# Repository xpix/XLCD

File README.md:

XStepperLCD
===========

LCD Module for XStepper

Some time ago, we designed and built version 1.0 of Xstepper.  Unlike other existing GRBL-based CNC solutions, Xstepper is an all-in-one device.  The possibility of controlling the machine in a headless state may be possible, and the first step toward doing so is some sort of visual display.  This module aims at solving part of the problem!

But how?  The good people coding GRBL dont have the on-chip memory to code in an LCD interface for GRBL.  Add to that the severe lack of available IO and this seems to rule out this type of expansion.  However, there is always a workaround.

This module spies on the serial communication between the arduino and PC using an ATtiny85.  Simultaneously the ATtimy polls the position of the spindle from the XStepper.  The returned data is then parsed and displayed on a local LCD.  You can choose to display the debug screen, work position or machine position using the on-board button.

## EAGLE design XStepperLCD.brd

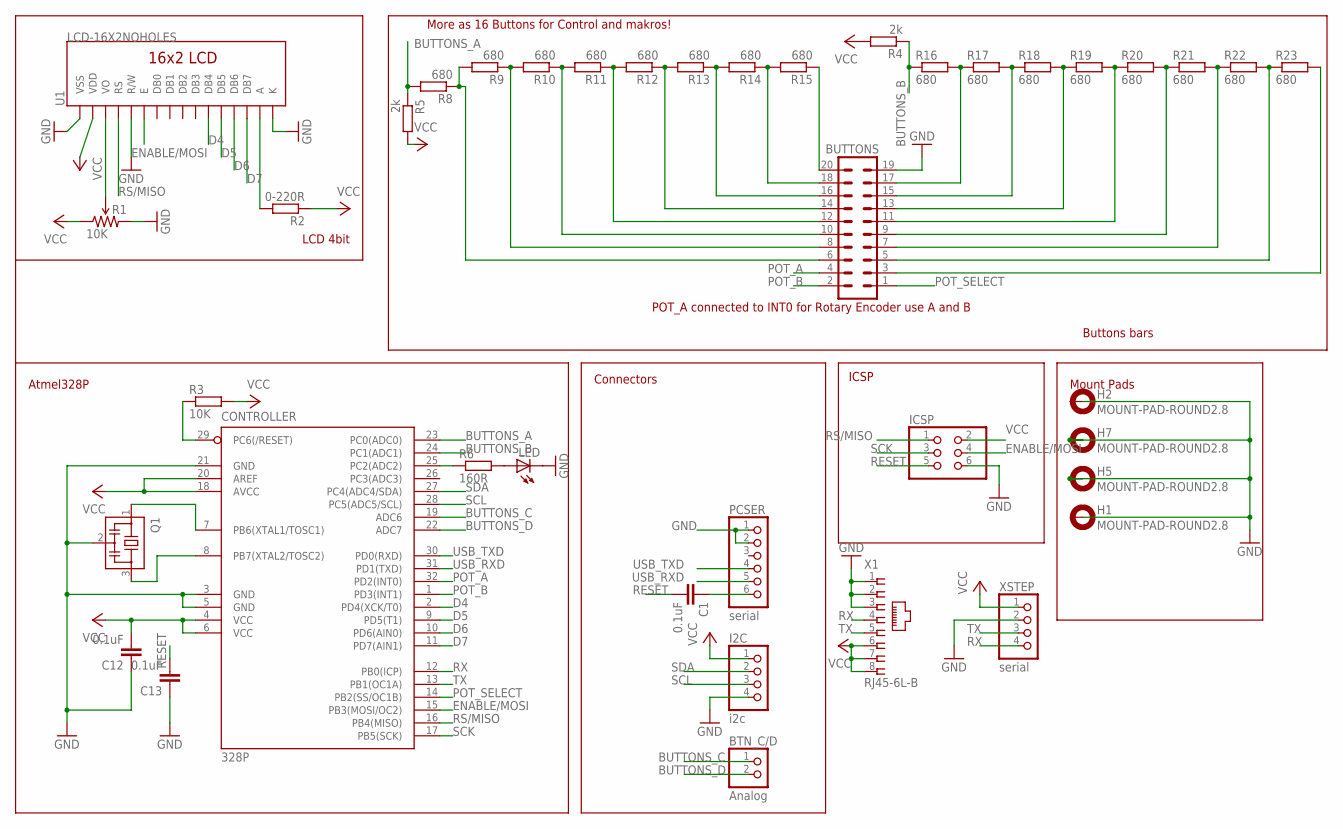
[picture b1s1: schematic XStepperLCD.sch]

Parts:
328P: CONTROLLER; TQFP32-08
BTN_C/D: Analog; 1X02
BUTTONS: ML20
C1, C12, C13: 0.1uF; C1206
H1, H2, H5, H7: MOUNT-PAD-ROUND2.8; 2,8-PAD
I2C: i2c; 1X04/90
ICSP: PINHD-2X3; 2X03
LED: LEDSMT1206; 1206
PCSER: serial; 1X06/90
Q1: CSTCR6M00G53Z; CSTCR6M
R1: 10K; 3362U-2
R2: 0-220R; R1206
R3: 10K; R1206
R4, R5: 2k; R1206
R6: 160R; R1206
R8, R9, R10, R11, R12, R13, R14, R15, R16, R17, R18, R19, R20, R21, R22, R23: 680; R1206
U1: LCD-16X2NOHOLES; LCD-16X2_NOHOLES
X1: RJ45-6L-B; RJ45-NO-SHIELD
XSTEP: serial; 1X04/90

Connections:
BUTTONS_A: 328P.23 (PC0(ADC0)), R5.1, R8.2
BUTTONS_B: 328P.24 (PC1(ADC1)), R4.1, R16.1
BUTTONS_C: 328P.19 (ADC6), BTN_C/D.1
BUTTONS_D: 328P.22 (ADC7), BTN_C/D.2
D4: 328P.2 (PD4(XCK/T0)), U1.11 (DB4)
D5: 328P.9 (PD5(T1)), U1.12 (DB5)
D6: 328P.10 (PD6(AIN0)), U1.13 (DB6)
D7: 328P.11 (PD7(AIN1)), U1.14 (DB7)
ENABLE/MOSI: 328P.15 (PB3(MOSI/OC2)), ICSP.4, U1.6 (E)
GND: 328P.3 (GND), 328P.5 (GND), 328P.21 (GND), BUTTONS.19, C12.1, C13.1, H5.B2,8, H7.B2,8, I2C.4, ICSP.6, LED.C, PCSER.1, PCSER.2, Q1.2, R1.3 (CW), U1.1 (VSS), U1.5 (R/W), U1.16 (K), X1.1, X1.2, X1.3, XSTEP.2
unnamed: R1.2 (WIPER), U1.3 (VO)
unnamed: R2.2, U1.15 (A)
unnamed: 328P.7 (PB6(XTAL1/TOSC1)), Q1.1
unnamed: BUTTONS.3, R23.2
unnamed: BUTTONS.6, R8.1, R9.2
unnamed: BUTTONS.8, R9.1, R10.2
unnamed: BUTTONS.10, R10.1, R11.2
unnamed: BUTTONS.12, R11.1, R12.2
unnamed: BUTTONS.16, R13.1, R14.2
unnamed: BUTTONS.18, R14.1, R15.2
unnamed: BUTTONS.14, R12.1, R13.2
unnamed: BUTTONS.20, R15.1
unnamed: LED.A, R6.2
unnamed: C1.1, PCSER.6
unnamed: 328P.25 (PC2(ADC2)), R6.1
unnamed: BUTTONS.17, R16.2, R17.1
unnamed: BUTTONS.15, R17.2, R18.1
unnamed: BUTTONS.13, R18.2, R19.1
unnamed: BUTTONS.11, R19.2, R20.1
unnamed: BUTTONS.9, R20.2, R21.1
unnamed: BUTTONS.7, R21.2, R22.1
unnamed: BUTTONS.5, R22.2, R23.1
unnamed: 328P.8 (PB7(XTAL2/TOSC2)), Q1.3
POT_A: 328P.32 (PD2(INT0)), BUTTONS.4
POT_B: 328P.1 (PD3(INT1)), BUTTONS.2
POT_SELECT: 328P.14 (PB2(SS/OC1B)), BUTTONS.1
RS/MISO: 328P.16 (PB4(MISO)), ICSP.1, U1.4 (RS)
RX: 328P.12 (PB0(ICP)), X1.4, XSTEP.4
SCK: 328P.17 (PB5(SCK)), ICSP.3
SCL: 328P.28 (PC5(ADC5/SCL)), I2C.3
SDA: 328P.27 (PC4(ADC4/SDA)), I2C.2
TX: 328P.13 (PB1(OC1A)), X1.5, XSTEP.3
USB_RXD: 328P.31 (PD1(TXD)), PCSER.5
USB_TXD: 328P.30 (PD0(RXD)), PCSER.4
VCC: 328P.4 (VCC), 328P.6 (VCC), 328P.18 (AVCC), 328P.20 (AREF), C12.2, I2C.1, ICSP.2, R1.1 (CCW), R2.1, R3.2, R4.2, R5.2, U1.2 (VDD), X1.6, X1.7, X1.8, XSTEP.1

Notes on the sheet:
Connectors
ICSP
Atmel328P
Mount Pads
Buttons bars
LCD 4bit
POT_A connected to INT0 for Rotary Encoder use A and B
More as 16 Buttons for Control and makros!

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
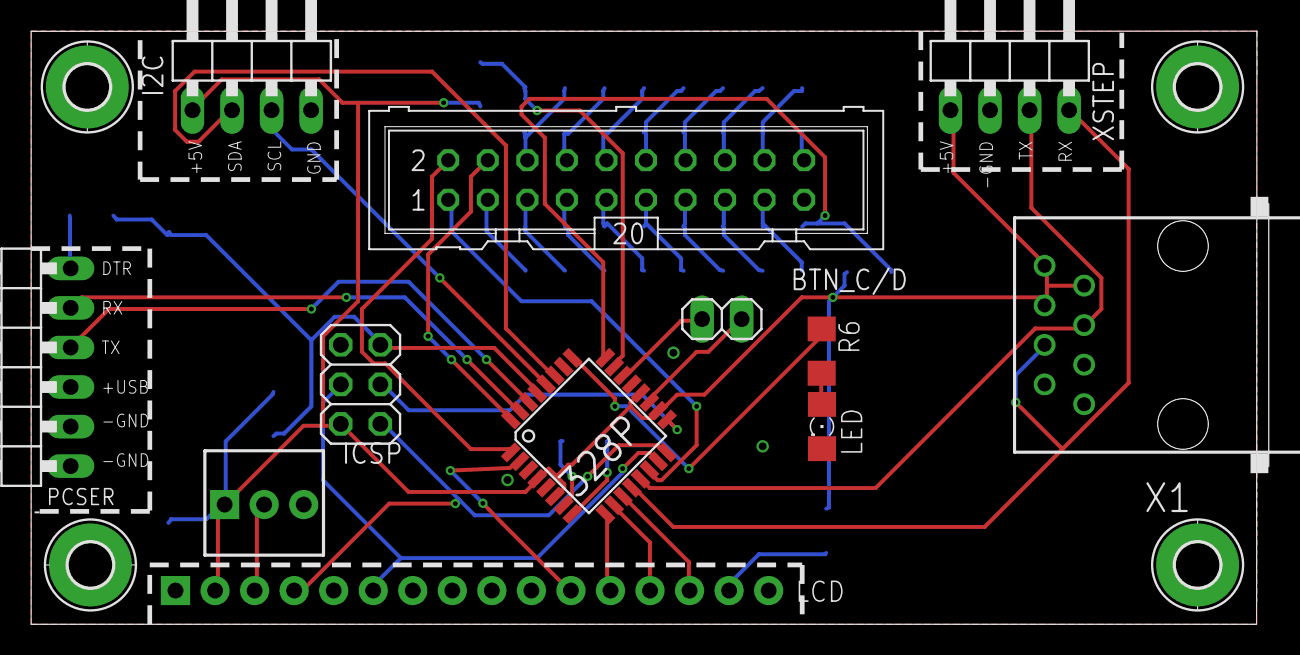
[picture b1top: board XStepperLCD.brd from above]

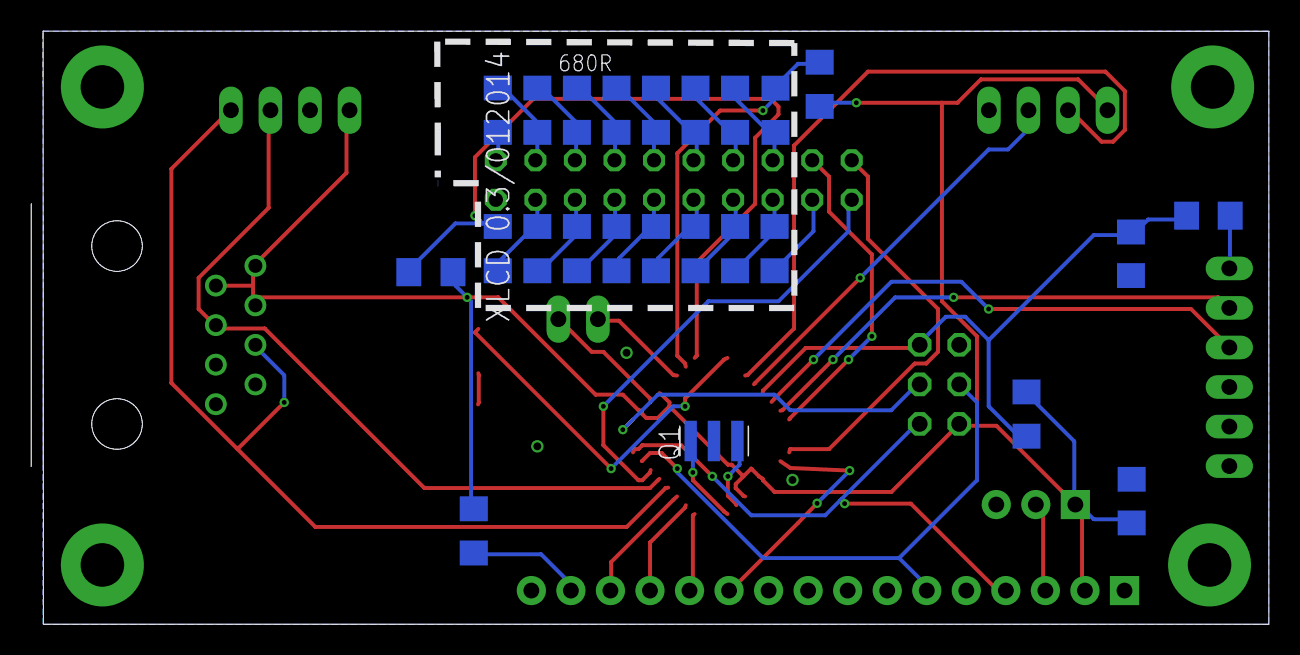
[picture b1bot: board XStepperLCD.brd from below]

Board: 2 copper layers, 79.5 x 38.1 mm, 40 parts (24 on the bottom side), 46 nets.

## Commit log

2013-07-17 first version
    - add first board and schema design
    - add first code for atiny85
2013-07-17 add some 3d images for design and readme
2013-07-19 Change from attiny to uno
    Change all from tiny to uno, cuz problems memory lwak or to small. First
    alpha testversion run :)
2013-07-19 Correct README from Matt
2013-07-22 add Software Serial
    - add software serial to spy the TX Line
    - dont display parse not succesfully
2013-07-22 add some comments
    - add some comments for forum
    - change display numbers format
2013-07-22 - add code for my terrible LCD
    - add some comments
2013-07-23 add config for my I2C LCD
2013-07-26 First konzept for XLCD with 328p
2013-07-30 add conn header for buttons
2013-08-01 pov, duo led, sketchup
    - add duo led
    - add icsp header
    - create povray file
2013-08-02 - add 2 connects for potentiometers
2013-08-08 - published to ITEAD order number 100015612
    - official Version XLCD 0.1
    - add some text
    - 3 pin header
    - changes from Matt
    - GND Polygon fix
2013-08-08 - forget one file
2013-08-09 - add some pics
2013-08-12 - use AltSoftSerial
    - first running version as SerialProxy
    - 2 tests with big gcode file send to Xstepper and display Data on LCD
    - remove Timer solution and test every line
2013-08-14 - add test menu with LCDMenuLib
2013-08-15 - software: add serial menu
    - add commands only for Xlcd with started colon
    - add threads to send every x seconds commands to grbl
    - split functions in separate files
2013-08-16 - add button thread
    - add output for UGS to ignore this
    - add command setinterval
    - add command memoryfree
    - add old buttons
    - use liquidfast
    - add read_buttons
2013-08-19 - add button_config file for users
    - change voltage array for 680 ohm network
    - stop all thread to test buttons
    - change some textmessages
    - fix button analyse
2013-08-20 - rename all mySerial to grblSerial
    - add and use phi_interfaces for rotary encoder
    - change intervall to 500ms and 1000ms for threads
    - send reset if connected to grbl for UniversalGcodeSender
    - add call_button
2013-08-29 - create branch for first version
2013-08-29 - damn, misstake with branches work on master
    - add a lot changes for LCDMenu
    - use phi_interfaces for analog buttons
    - remove a lot unused code
2013-08-30 - switch back to altsoftserial
2013-08-30 - add all features from last master step by step to found a crash bug
2013-09-13 - change to 0.2 and produce pcb
    - change all resistors and caps to SMD 1206
    - change RX/TX Wires to USB_RXD/USB_TXD
    - move RX/TX to Pin 14 and pin 15
    - use Pin 4,5 for RotaryEncoder
    - use POT_Select on Pin 16
    - move Enable to mosi pin
2013-10-09 - get pcb's and add some photos, smal code changes
    - remove LCDMenu, cuz need to much memory
    - change all pins to 0.2
    - add pov files
2013-10-23 - get button values only from A0
    - stop/restart all threads in get values command
    - refresh silkscreen in board and design
    - set version 0.2 in code
    - remove some comments
    - add group init for threads
    - reformat code
2013-10-25 - bugfic: set all buttons resistor to different values
    - fix schema and board
    - fix some typos and bugs in readButtons
    - add thread to read buttons
2013-10-30 - create define area for users
    - remove unuded code and comments
2013-11-04 - fix serial speed data and button routine
2013-11-06 - first run version with UGS
    - add func state to discover state from machine
    - call button functions only if first analog pin set
    - call getPosition only if not called from client in last interval time
2013-11-07 - allow :i -1 to stop interval
    - remove about
    - fix call_button(s) for PinB
2013-11-14 - add clear for every row in LCD
2014-01-21 - replace some TH parts with SMD and bugfixes
    - remove reset button
    - remove power pin and choose only power from xstepper
    - add RJ45 plugin for connect XStepper
    - change all button resistors to 680r and connect serial
    - remove LED from serial line and put a new one to A7
    - add some text to I2C
2014-05-22 make board bigger
2014-08-18 finish to produce
    Route new and set some via's.

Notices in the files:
parts and their libraries:
SparkFun-Electromechanical: Licensing: CC v3.0 Share-Alike You are welcome to use this library for commercial purposes.
